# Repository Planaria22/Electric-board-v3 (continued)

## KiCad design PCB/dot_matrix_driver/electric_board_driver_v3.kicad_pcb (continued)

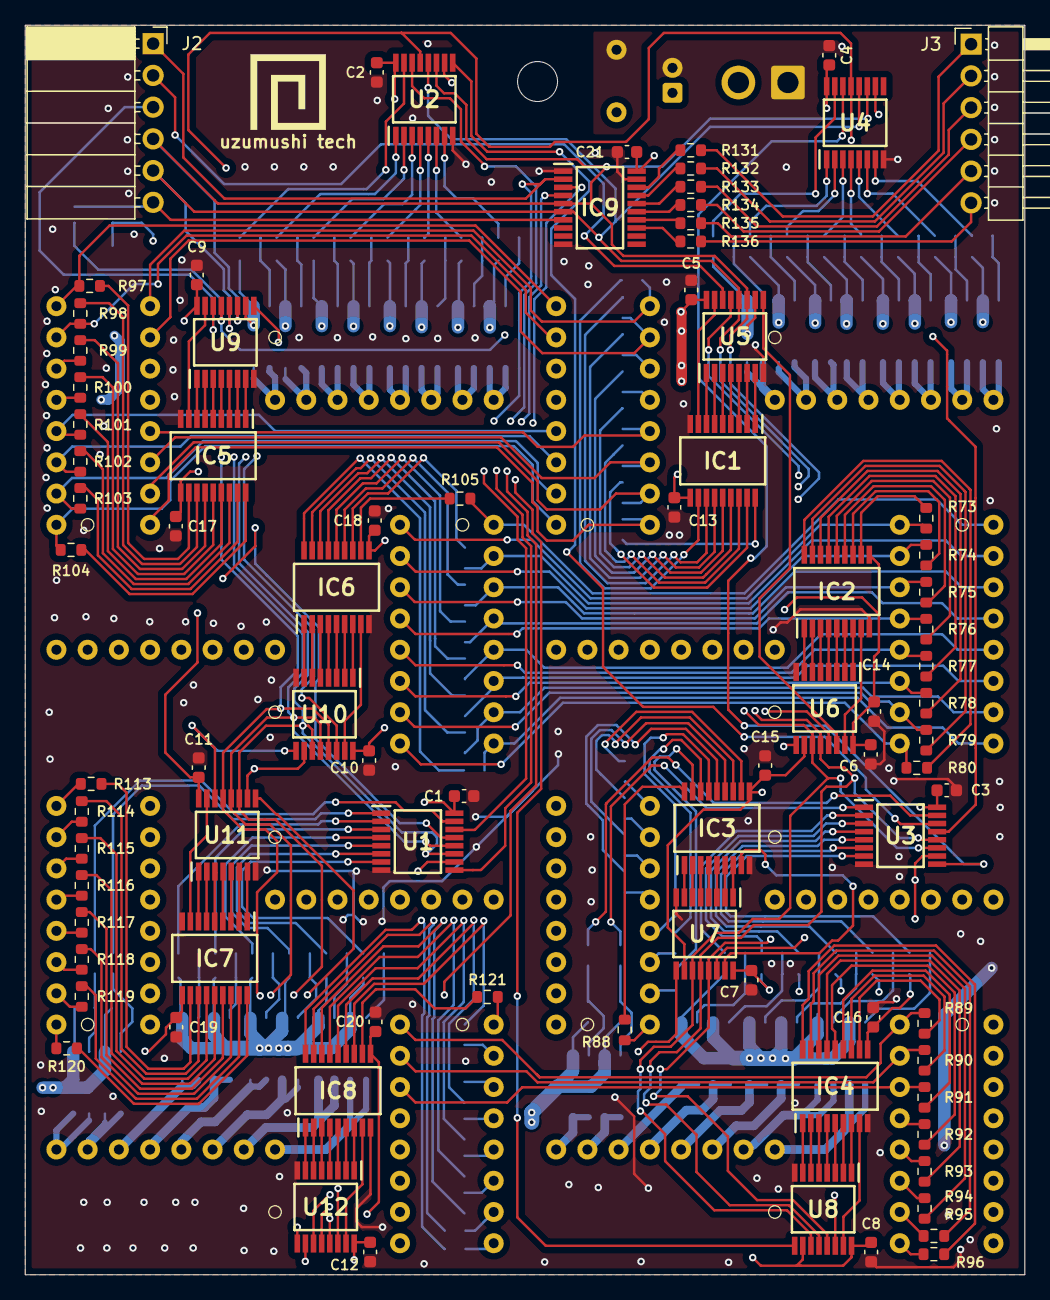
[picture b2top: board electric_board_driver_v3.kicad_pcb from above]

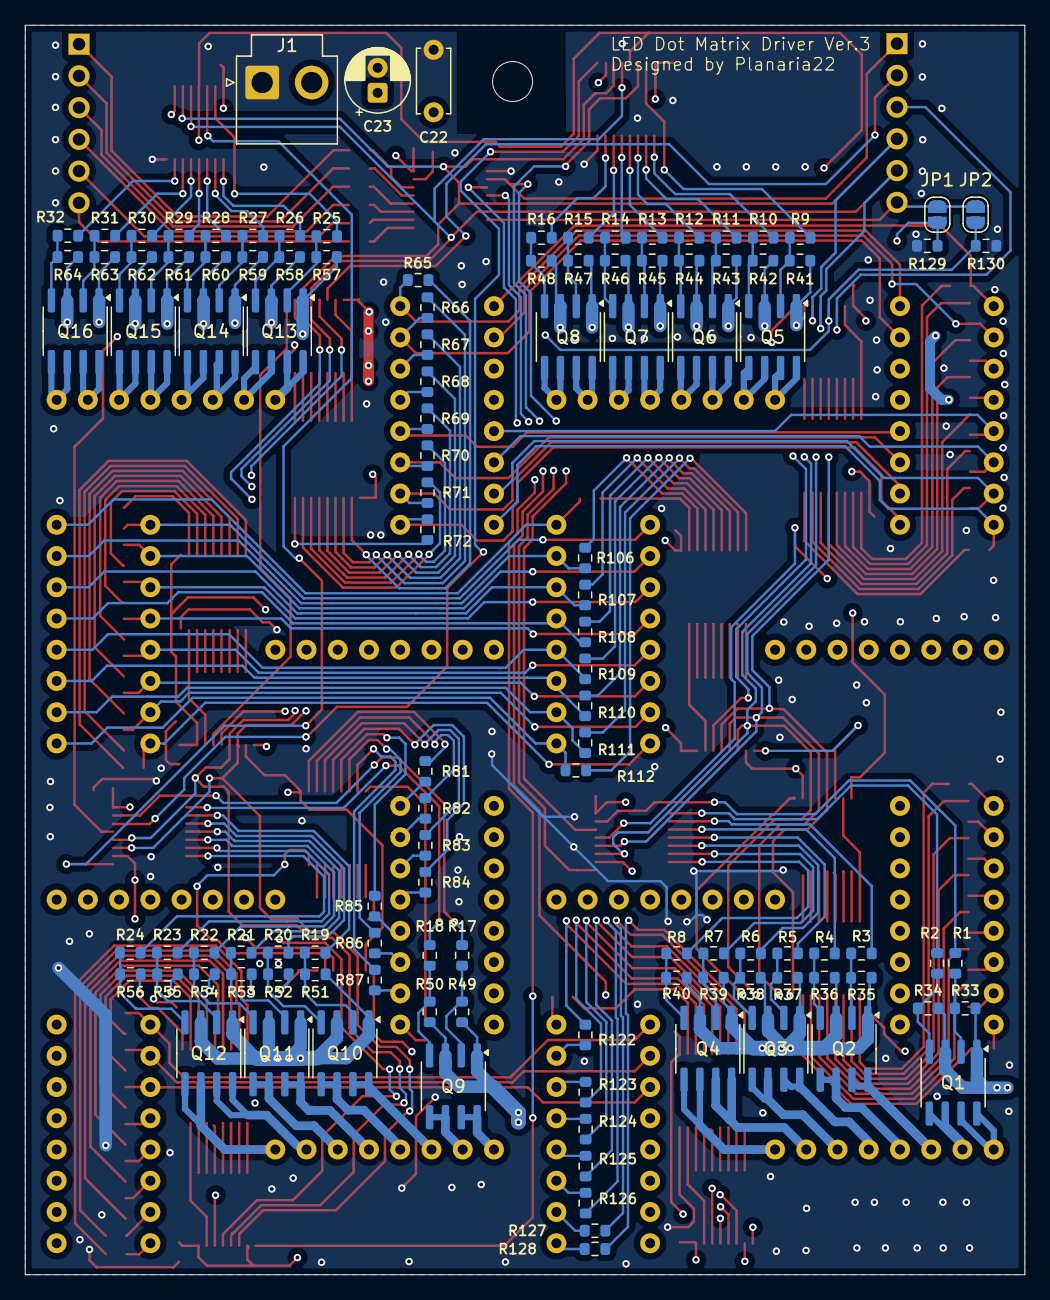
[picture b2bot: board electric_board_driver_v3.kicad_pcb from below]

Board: 4 copper layers, 80.0 x 100.0 mm, 206 parts (116 on the bottom side), 321 nets.
